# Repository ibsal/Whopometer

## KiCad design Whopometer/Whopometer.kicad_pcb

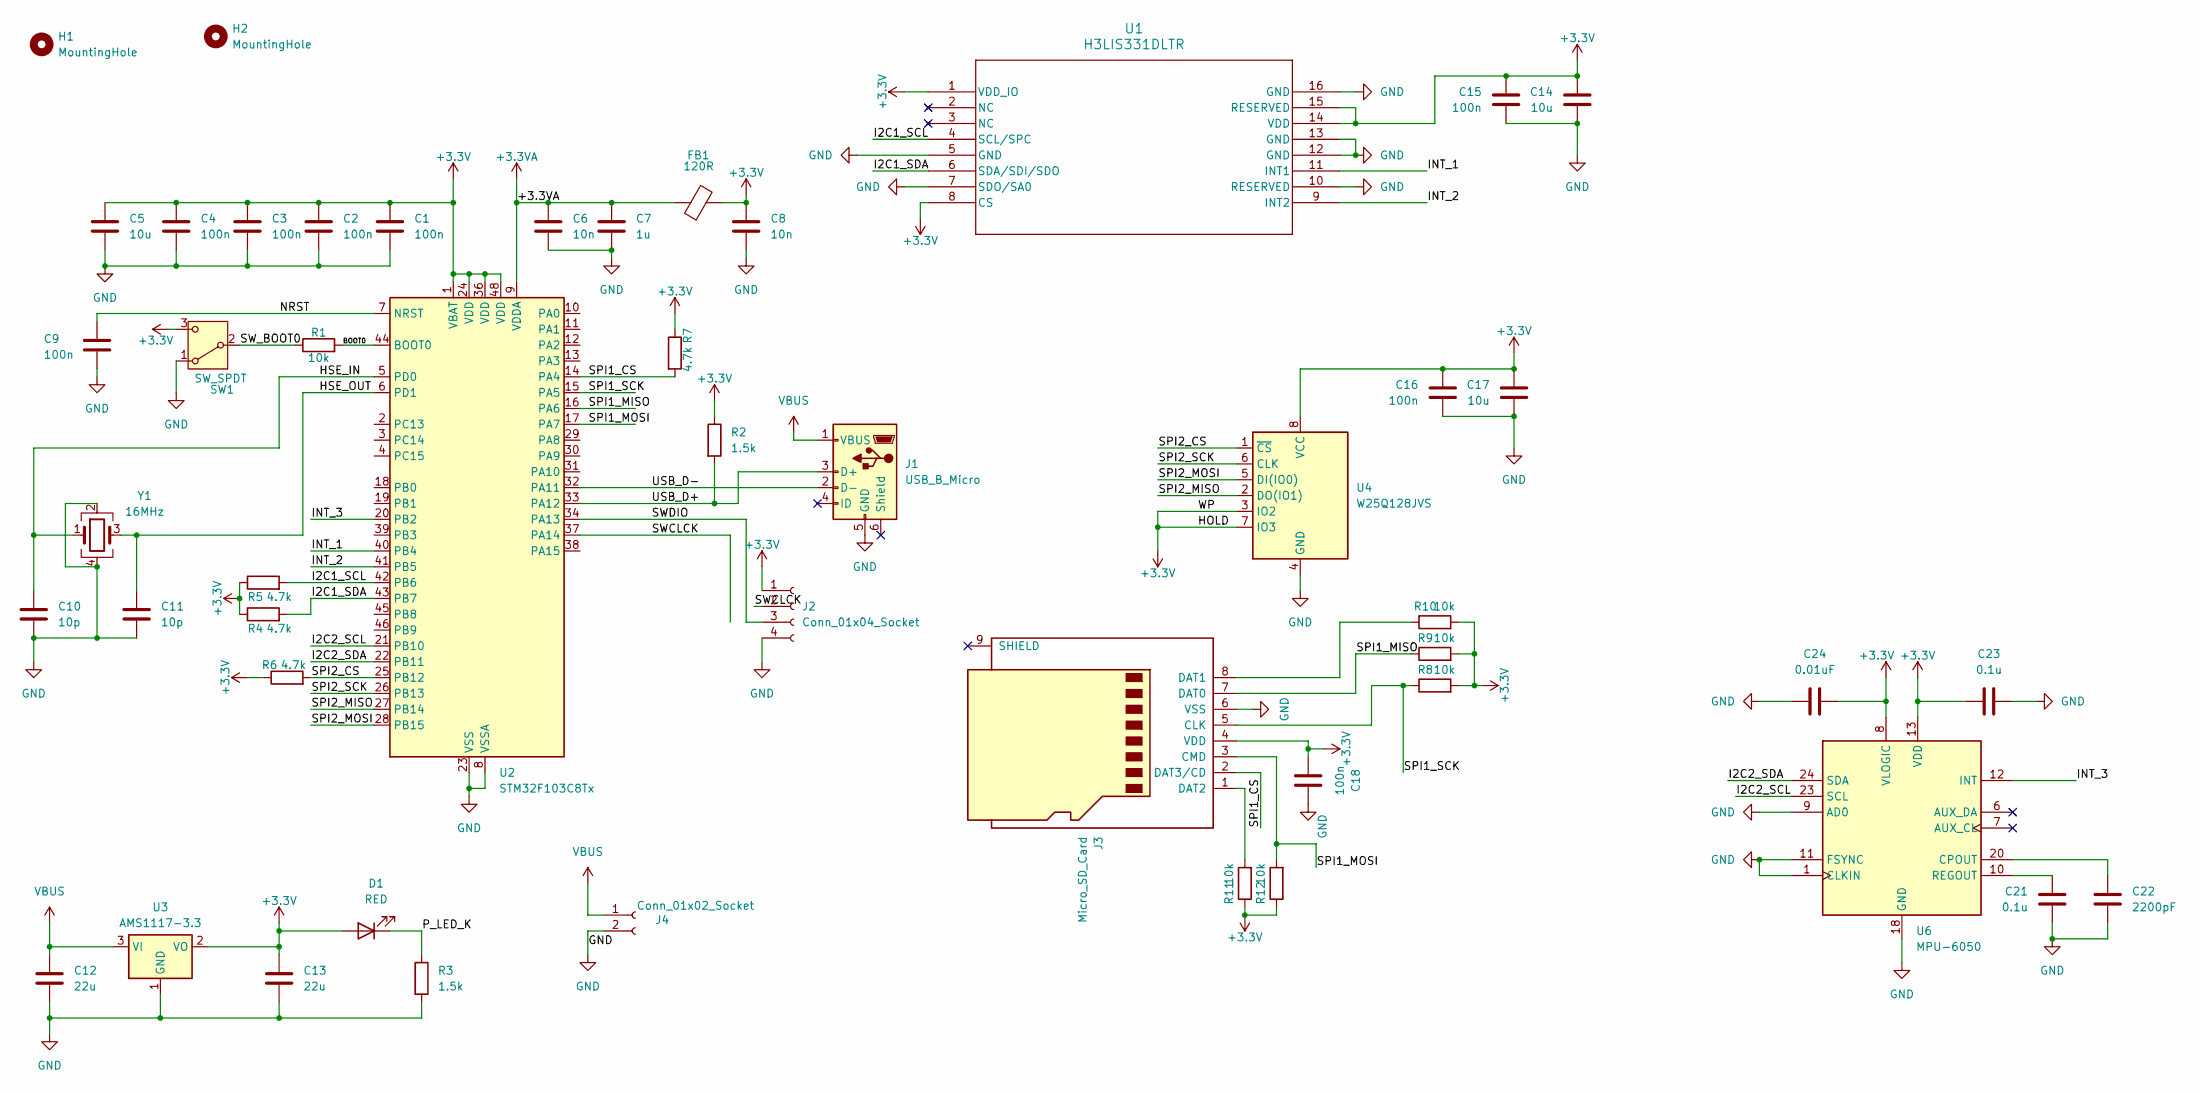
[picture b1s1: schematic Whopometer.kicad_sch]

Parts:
C1, C2, C3, C4, C9, C15, C16, C18: 100n; C_0201_0603Metric
C5, C14, C17: 10u; C_0201_0603Metric
C6, C8: 10n; C_0201_0603Metric
C7: 1u; C_0201_0603Metric
C10, C11: 10p; C_0201_0603Metric
C12, C13: 22u; C_0201_0603Metric
C21, C23: 0.1u; C_0201_0603Metric
C22: 2200pF; C_0201_0603Metric
C24: 0.01uF; C_0201_0603Metric
D1: RED; LED_0805_2012Metric
FB1: 120R; L_0805_2012Metric
H1, H2: MountingHole; MountingHole_2.2mm_M2_ISO7380_Pad
J1: USB_B_Micro; USB_Micro-B_Amphenol_10104110_Horizontal
J2: Conn_01x04_Socket; PinHeader_1x04_P2.00mm_Horizontal
J3: Micro_SD_Card; microSD_HC_Molex_104031-0811
J4: Conn_01x02_Socket; PinHeader_1x02_P2.00mm_Horizontal
R1, R8, R9, R10, R11, R12: 10k; R_0603_1608Metric
R2, R3: 1.5k; R_0603_1608Metric
R4, R5, R6, R7: 4.7k; R_0603_1608Metric
SW1: SW_SPDT; SW_SPDT_PCM12
U1: H3LIS331DLTR; QFN_31DLTR_STM
U2: STM32F103C8Tx; LQFP-48_7x7mm_P0.5mm
U3: AMS1117-3.3; SOT-223-3_TabPin2
U4: W25Q128JVS; SOIC-8_5.23x5.23mm_P1.27mm
U6: MPU-6050; InvenSense_QFN-24_4x4mm_P0.5mm
Y1: 16MHz; Crystal_SMD_3225-4Pin_3.2x2.5mm

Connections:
+3.3V: C1.1, C2.1, C3.1, C4.1, C5.1, C8.1, C13.1, C14.1, C15.1, C16.1, C17.1, C18.1, C23.2, C24.1, D1.2 (A), FB1.2, J2.1, J3.4 (VDD), R2.1, R4.1, R5.1, R6.1, R7.1, R8.2, R9.2, R10.2, R11.1, R12.1, SW1.3 (C), U1.1 (VDD_IO), U1.8 (CS), U1.14 (VDD), U1.15 (RESERVED), U2.1 (VBAT), U2.24 (VDD), U2.36 (VDD), U2.48 (VDD), U3.2 (VO), U4.3 (IO2), U4.7 (IO3), U4.8 (VCC), U6.8 (VLOGIC), U6.13 (VDD)
+3.3VA: C6.1, C7.1, FB1.1, U2.9 (VDDA)
/BOOT0: R1.2, U2.44 (BOOT0)
/HSE_IN: C10.1, U2.5 (PD0), Y1.1
/HSE_OUT: C11.1, U2.6 (PD1), Y1.3
/I2C1_SCL: R5.2, U1.4 (SCL/SPC), U2.42 (PB6)
/I2C1_SDA: R4.2, U1.6 (SDA/SDI/SDO), U2.43 (PB7)
/I2C2_SCL: U2.21 (PB10), U6.23 (SCL)
/I2C2_SDA: U2.22 (PB11), U6.24 (SDA)
/INT_1: U1.11 (INT1), U2.40 (PB4)
/INT_2: U1.9 (INT2), U2.41 (PB5)
/INT_3: U2.20 (PB2), U6.12 (INT)
/NRST: C9.1, U2.7 (NRST)
/P_LED_K: D1.1 (K), R3.1
/SPI1_CS: J3.2 (DAT3/CD), R7.2, U2.14 (PA4)
/SPI1_MISO: J3.7 (DAT0), R9.1, U2.16 (PA6)
/SPI1_MOSI: J3.3 (CMD), R12.2, U2.17 (PA7)
/SPI1_SCK: J3.5 (CLK), R8.1, U2.15 (PA5)
/SPI2_CS: R6.2, U2.25 (PB12), U4.1 (~CS)
/SPI2_MISO: U2.27 (PB14), U4.2 (DO(IO1))
/SPI2_MOSI: U2.28 (PB15), U4.5 (DI(IO0))
/SPI2_SCK: U2.26 (PB13), U4.6 (CLK)
/SWCLCK: J2.2, U2.37 (PA14)
/SWDIO: J2.3, U2.34 (PA13)
/SW_BOOT0: R1.1, SW1.2 (B)
/USB_D+: J1.3 (D+), R2.2, U2.33 (PA12)
/USB_D-: J1.2 (D-), U2.32 (PA11)
GND: C1.2, C2.2, C3.2, C4.2, C5.2, C6.2, C7.2, C8.2, C9.2, C10.2, C11.2, C12.2, C13.2, C14.2, C15.2, C16.2, C17.2, C18.2, C21.1, C22.2, C23.1, C24.2, J1.5 (GND), J2.4, J3.6 (VSS), J4.2, R3.2, SW1.1 (A), U1.5 (GND), U1.7 (SDO/SA0), U1.10 (RESERVED), U1.12 (GND), U1.13 (GND), U1.16 (GND), U2.8 (VSSA), U2.23 (VSS), U2.35 (VSS), U2.47 (VSS), U3.1 (GND), U4.4 (GND), U6.1 (CLKIN), U6.9 (AD0), U6.11 (FSYNC), U6.18 (GND), Y1.2, Y1.4
unnamed: J3.8 (DAT1), R10.1
unnamed: J3.1 (DAT2), R11.2
unnamed: C22.1, U6.20 (CPOUT)
unnamed: C21.2, U6.10 (REGOUT)
VBUS: C12.1, J1.1 (VBUS), J4.1, U3.3 (VI)

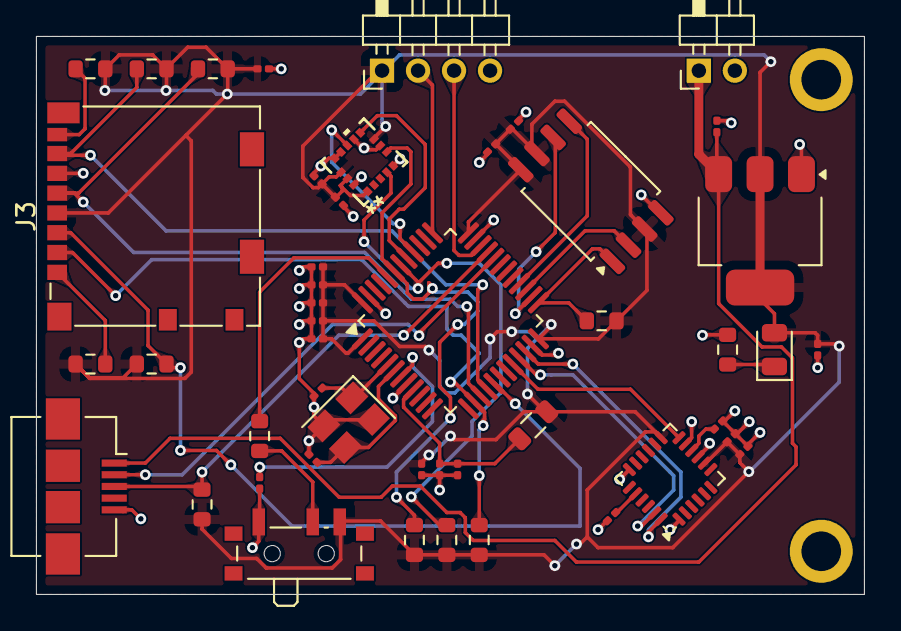
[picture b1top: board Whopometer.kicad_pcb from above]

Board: 2 copper layers, 46.0 x 31.0 mm, 49 parts (0 on the bottom side), 33 nets.

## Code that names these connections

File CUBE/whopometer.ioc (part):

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Mcu.Name=STM32F103C(8-B)Tx
Mcu.Package=LQFP48
Mcu.UserName=STM32F103C8Tx
PA11.Mode=Device
PA11.Signal=USB_DM
PA12.Mode=Device
PA12.Signal=USB_DP
PA13.Mode=Serial_Wire
PA13.Signal=SYS_JTMS-SWDIO
PA14.Mode=Serial_Wire
PA14.Signal=SYS_JTCK-SWCLK
PA4.GPIOParameters=GPIO_Label
PA4.GPIO_Label=SD_CS
PA4.Signal=GPIO_Output
PA5.Mode=Full_Duplex_Master
PA5.Signal=SPI1_SCK
PA6.Mode=Full_Duplex_Master
PA6.Signal=SPI1_MISO
PA7.Mode=Full_Duplex_Master
PA7.Signal=SPI1_MOSI
PB10.Mode=I2C
PB10.Signal=I2C2_SCL
PB11.Mode=I2C
PB11.Signal=I2C2_SDA
PB13.Mode=Full_Duplex_Master
PB13.Signal=SPI2_SCK
PB14.Mode=Full_Duplex_Master
PB14.Signal=SPI2_MISO
PB15.Mode=Full_Duplex_Master
PB15.Signal=SPI2_MOSI
PB2.Signal=GPIO_Input
PB4.Signal=GPIO_Input
PB6.Mode=I2C
PB6.Signal=I2C1_SCL
PB7.Mode=I2C
PB7.Signal=I2C1_SDA
PD0-OSC_IN.Mode=HSE-External-Oscillator
PD0-OSC_IN.Signal=RCC_OSC_IN
PD1-OSC_OUT.Mode=HSE-External-Oscillator
PD1-OSC_OUT.Signal=RCC_OSC_OUT
RCC.HSEDivPLL=RCC_HSE_PREDIV_DIV2
RCC.HSE_VALUE=16000000
RCC.SYSCLKFreq_VALUE=72000000
RCC.SYSCLKSource=RCC_SYSCLKSOURCE_PLLCLK
board=custom

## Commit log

2024-11-27 Added IMU library
2024-11-27 uhhh let me be clear
2024-12-01 started stm32 schematic
2024-12-02 STM 32 time
2024-12-26 Yuppers
2025-02-08 DID IT WORK
2025-02-20 yay firmware
2025-02-20 Serial over usb added
2025-02-24 Added high G accelerometer driver
2025-02-25 yipeee
2025-02-25 Now it works!
2025-02-25 Micro SD Drivers
2025-02-25 Increase record length to 3 minutes
2025-02-25 Increase sample rate to 1khz
